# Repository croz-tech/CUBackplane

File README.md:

# Control Universal 4-Slot DIN41612 Backplane
***Note: Early preview only... at this time this board has not been fabricated/tested***

A 4 slot DIN 41612 backplane for use with the EuroBEEB and compatible cards

- Designed in KiCAD, in addition to giving 4x DIN connectors on a 1" (5HP spacing) allowing mounting in a 24HP enclosure with 2HP blanking plates at either end.
- Board has pads for power supply inputs (actually only +5V and GND are needed for a standard EuroBEEB) and test points for access to all Data, Control and Address lines.  These TPs are labelled on the under/back side for easy access when this is mounted in a rack.  The TPs are on a 0.1" pitch, so headers can be used if desired.
- Board is <100x100mm so should be low-cost fabrication.

Note that this isn't strictly a 'backplane' in the DIN enclosure sense.  Rather than mounting the PCB to 'backplane' fixtures in an enclosure, the PCB should simply be soldered across the row of vertical DIN female connectors and then the connectors mounted to specific connector mounting rails.  Please take this into consideration if ordering enclosure parts from Verotec or your preferred enclosure supplier.

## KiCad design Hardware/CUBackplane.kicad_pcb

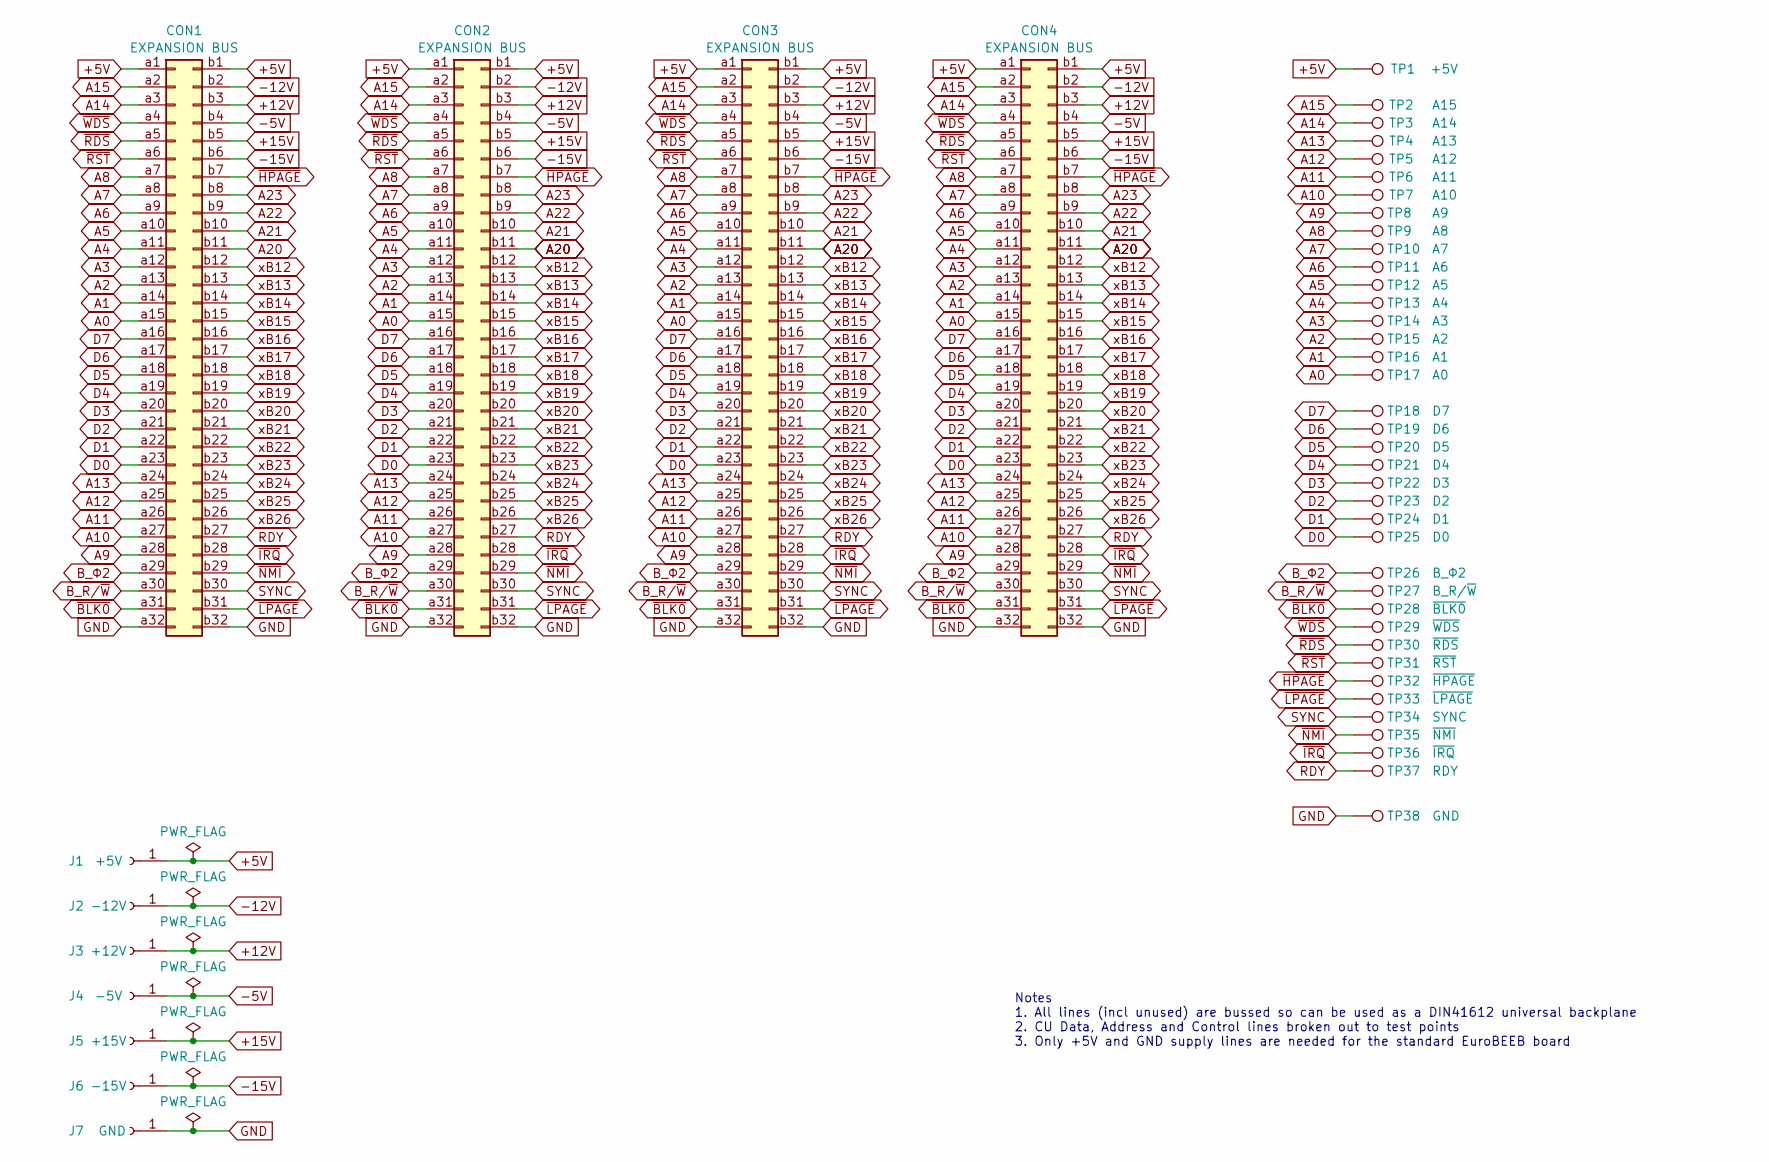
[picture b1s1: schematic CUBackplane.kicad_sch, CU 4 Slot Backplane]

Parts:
CON1, CON2, CON3, CON4: EXPANSION BUS; DIN41612_B_2x32_Female_Vertical_THT
J1: +5V; TestPoint_THTPad_D3.0mm_Drill1.5mm
J2: -12V; TestPoint_THTPad_D2.0mm_Drill1.0mm
J3: +12V; TestPoint_THTPad_D2.0mm_Drill1.0mm
J4: -5V; TestPoint_THTPad_D2.0mm_Drill1.0mm
J5: +15V; TestPoint_THTPad_D2.0mm_Drill1.0mm
J6: -15V; TestPoint_THTPad_D2.0mm_Drill1.0mm
J7: GND; TestPoint_THTPad_D3.0mm_Drill1.5mm
TP1: +5V; TestPoint_THTPad_D1.5mm_Drill0.7mm
TP2: A15; TestPoint_THTPad_D1.5mm_Drill0.7mm
TP3: A14; TestPoint_THTPad_D1.5mm_Drill0.7mm
TP4: A13; TestPoint_THTPad_D1.5mm_Drill0.7mm
TP5: A12; TestPoint_THTPad_D1.5mm_Drill0.7mm
TP6: A11; TestPoint_THTPad_D1.5mm_Drill0.7mm
TP7: A10; TestPoint_THTPad_D1.5mm_Drill0.7mm
TP8: A9; TestPoint_THTPad_D1.5mm_Drill0.7mm
TP9: A8; TestPoint_THTPad_D1.5mm_Drill0.7mm
TP10: A7; TestPoint_THTPad_D1.5mm_Drill0.7mm
TP11: A6; TestPoint_THTPad_D1.5mm_Drill0.7mm
TP12: A5; TestPoint_THTPad_D1.5mm_Drill0.7mm
TP13: A4; TestPoint_THTPad_D1.5mm_Drill0.7mm
TP14: A3; TestPoint_THTPad_D1.5mm_Drill0.7mm
TP15: A2; TestPoint_THTPad_D1.5mm_Drill0.7mm
TP16: A1; TestPoint_THTPad_D1.5mm_Drill0.7mm
TP17: A0; TestPoint_THTPad_D1.5mm_Drill0.7mm
TP18: D7; TestPoint_THTPad_D1.5mm_Drill0.7mm
TP19: D6; TestPoint_THTPad_D1.5mm_Drill0.7mm
TP20: D5; TestPoint_THTPad_D1.5mm_Drill0.7mm
TP21: D4; TestPoint_THTPad_D1.5mm_Drill0.7mm
TP22: D3; TestPoint_THTPad_D1.5mm_Drill0.7mm
TP23: D2; TestPoint_THTPad_D1.5mm_Drill0.7mm
TP24: D1; TestPoint_THTPad_D1.5mm_Drill0.7mm
TP25: D0; TestPoint_THTPad_D1.5mm_Drill0.7mm
TP26: B_Φ2; TestPoint_THTPad_D1.5mm_Drill0.7mm
TP27: B_R/~{W}; TestPoint_THTPad_D1.5mm_Drill0.7mm
TP28: ~{BLK0}; TestPoint_THTPad_D1.5mm_Drill0.7mm
TP29: ~{WDS}; TestPoint_THTPad_D1.5mm_Drill0.7mm
TP30: ~{RDS}; TestPoint_THTPad_D1.5mm_Drill0.7mm
TP31: ~{RST}; TestPoint_THTPad_D1.5mm_Drill0.7mm
TP32: ~{HPAGE}; TestPoint_THTPad_D1.5mm_Drill0.7mm
TP33: ~{LPAGE}; TestPoint_THTPad_D1.5mm_Drill0.7mm
TP34: SYNC; TestPoint_THTPad_D1.5mm_Drill0.7mm
TP35: ~{NMI}; TestPoint_THTPad_D1.5mm_Drill0.7mm
TP36: ~{IRQ}; TestPoint_THTPad_D1.5mm_Drill0.7mm
TP37: RDY; TestPoint_THTPad_D1.5mm_Drill0.7mm
TP38: GND; TestPoint_THTPad_D1.5mm_Drill0.7mm

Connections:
+5V: CON1.a1, CON1.b1, CON2.a1, CON2.b1, CON3.a1, CON3.b1, CON4.a1, CON4.b1, J1.1, TP1.1
+12V: CON1.b3, CON2.b3, CON3.b3, CON4.b3, J3.1
+15V: CON1.b5, CON2.b5, CON3.b5, CON4.b5, J5.1
-5V: CON1.b4, CON2.b4, CON3.b4, CON4.b4, J4.1
-12V: CON1.b2, CON2.b2, CON3.b2, CON4.b2, J2.1
-15V: CON1.b6, CON2.b6, CON3.b6, CON4.b6, J6.1
A0: CON1.a15, CON2.a15, CON3.a15, CON4.a15, TP17.1
A1: CON1.a14, CON2.a14, CON3.a14, CON4.a14, TP16.1
A2: CON1.a13, CON2.a13, CON3.a13, CON4.a13, TP15.1
A3: CON1.a12, CON2.a12, CON3.a12, CON4.a12, TP14.1
A4: CON1.a11, CON2.a11, CON3.a11, CON4.a11, TP13.1
A5: CON1.a10, CON2.a10, CON3.a10, CON4.a10, TP12.1
A6: CON1.a9, CON2.a9, CON3.a9, CON4.a9, TP11.1
A7: CON1.a8, CON2.a8, CON3.a8, CON4.a8, TP10.1
A8: CON1.a7, CON2.a7, CON3.a7, CON4.a7, TP9.1
A9: CON1.a28, CON2.a28, CON3.a28, CON4.a28, TP8.1
A10: CON1.a27, CON2.a27, CON3.a27, CON4.a27, TP7.1
A11: CON1.a26, CON2.a26, CON3.a26, CON4.a26, TP6.1
A12: CON1.a25, CON2.a25, CON3.a25, CON4.a25, TP5.1
A13: CON1.a24, CON2.a24, CON3.a24, CON4.a24, TP4.1
A14: CON1.a3, CON2.a3, CON3.a3, CON4.a3, TP3.1
A15: CON1.a2, CON2.a2, CON3.a2, CON4.a2, TP2.1
A20: CON1.b11, CON2.b11, CON3.b11, CON4.b11
A21: CON1.b10, CON2.b10, CON3.b10, CON4.b10
A22: CON1.b9, CON2.b9, CON3.b9, CON4.b9
A23: CON1.b8, CON2.b8, CON3.b8, CON4.b8
B_R/~W: CON1.a30, CON2.a30, CON3.a30, CON4.a30, TP27.1
B_Φ2: CON1.a29, CON2.a29, CON3.a29, CON4.a29, TP26.1
D0: CON1.a23, CON2.a23, CON3.a23, CON4.a23, TP25.1
D1: CON1.a22, CON2.a22, CON3.a22, CON4.a22, TP24.1
D2: CON1.a21, CON2.a21, CON3.a21, CON4.a21, TP23.1
D3: CON1.a20, CON2.a20, CON3.a20, CON4.a20, TP22.1
D4: CON1.a19, CON2.a19, CON3.a19, CON4.a19, TP21.1
D5: CON1.a18, CON2.a18, CON3.a18, CON4.a18, TP20.1
D6: CON1.a17, CON2.a17, CON3.a17, CON4.a17, TP19.1
D7: CON1.a16, CON2.a16, CON3.a16, CON4.a16, TP18.1
GND: CON1.a32, CON1.b32, CON2.a32, CON2.b32, CON3.a32, CON3.b32, CON4.a32, CON4.b32, J7.1, TP38.1
RDY: CON1.b27, CON2.b27, CON3.b27, CON4.b27, TP37.1
SYNC: CON1.b30, CON2.b30, CON3.b30, CON4.b30, TP34.1
xB12: CON1.b12, CON2.b12, CON3.b12, CON4.b12
xB13: CON1.b13, CON2.b13, CON3.b13, CON4.b13
xB14: CON1.b14, CON2.b14, CON3.b14, CON4.b14
xB15: CON1.b15, CON2.b15, CON3.b15, CON4.b15
xB16: CON1.b16, CON2.b16, CON3.b16, CON4.b16
xB17: CON1.b17, CON2.b17, CON3.b17, CON4.b17
xB18: CON1.b18, CON2.b18, CON3.b18, CON4.b18
xB19: CON1.b19, CON2.b19, CON3.b19, CON4.b19
xB20: CON1.b20, CON2.b20, CON3.b20, CON4.b20
xB21: CON1.b21, CON2.b21, CON3.b21, CON4.b21
xB22: CON1.b22, CON2.b22, CON3.b22, CON4.b22
xB23: CON1.b23, CON2.b23, CON3.b23, CON4.b23
xB24: CON1.b24, CON2.b24, CON3.b24, CON4.b24
xB25: CON1.b25, CON2.b25, CON3.b25, CON4.b25
xB26: CON1.b26, CON2.b26, CON3.b26, CON4.b26
~BLK0: CON1.a31, CON2.a31, CON3.a31, CON4.a31, TP28.1
~HPAGE: CON1.b7, CON2.b7, CON3.b7, CON4.b7, TP32.1
~IRQ: CON1.b28, CON2.b28, CON3.b28, CON4.b28, TP36.1
~LPAGE: CON1.b31, CON2.b31, CON3.b31, CON4.b31, TP33.1
~NMI: CON1.b29, CON2.b29, CON3.b29, CON4.b29, TP35.1
~RDS: CON1.a5, CON2.a5, CON3.a5, CON4.a5, TP30.1
~RST: CON1.a6, CON2.a6, CON3.a6, CON4.a6, TP31.1
~WDS: CON1.a4, CON2.a4, CON3.a4, CON4.a4, TP29.1

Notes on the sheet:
Notes 1. All lines (incl unused) are bussed so can be used as a DIN41612 universal backplane 2. CU Data, Address and Control lines broken out to test points 3. Only +5V and GND supply lines are needed for the standard EuroBEEB board

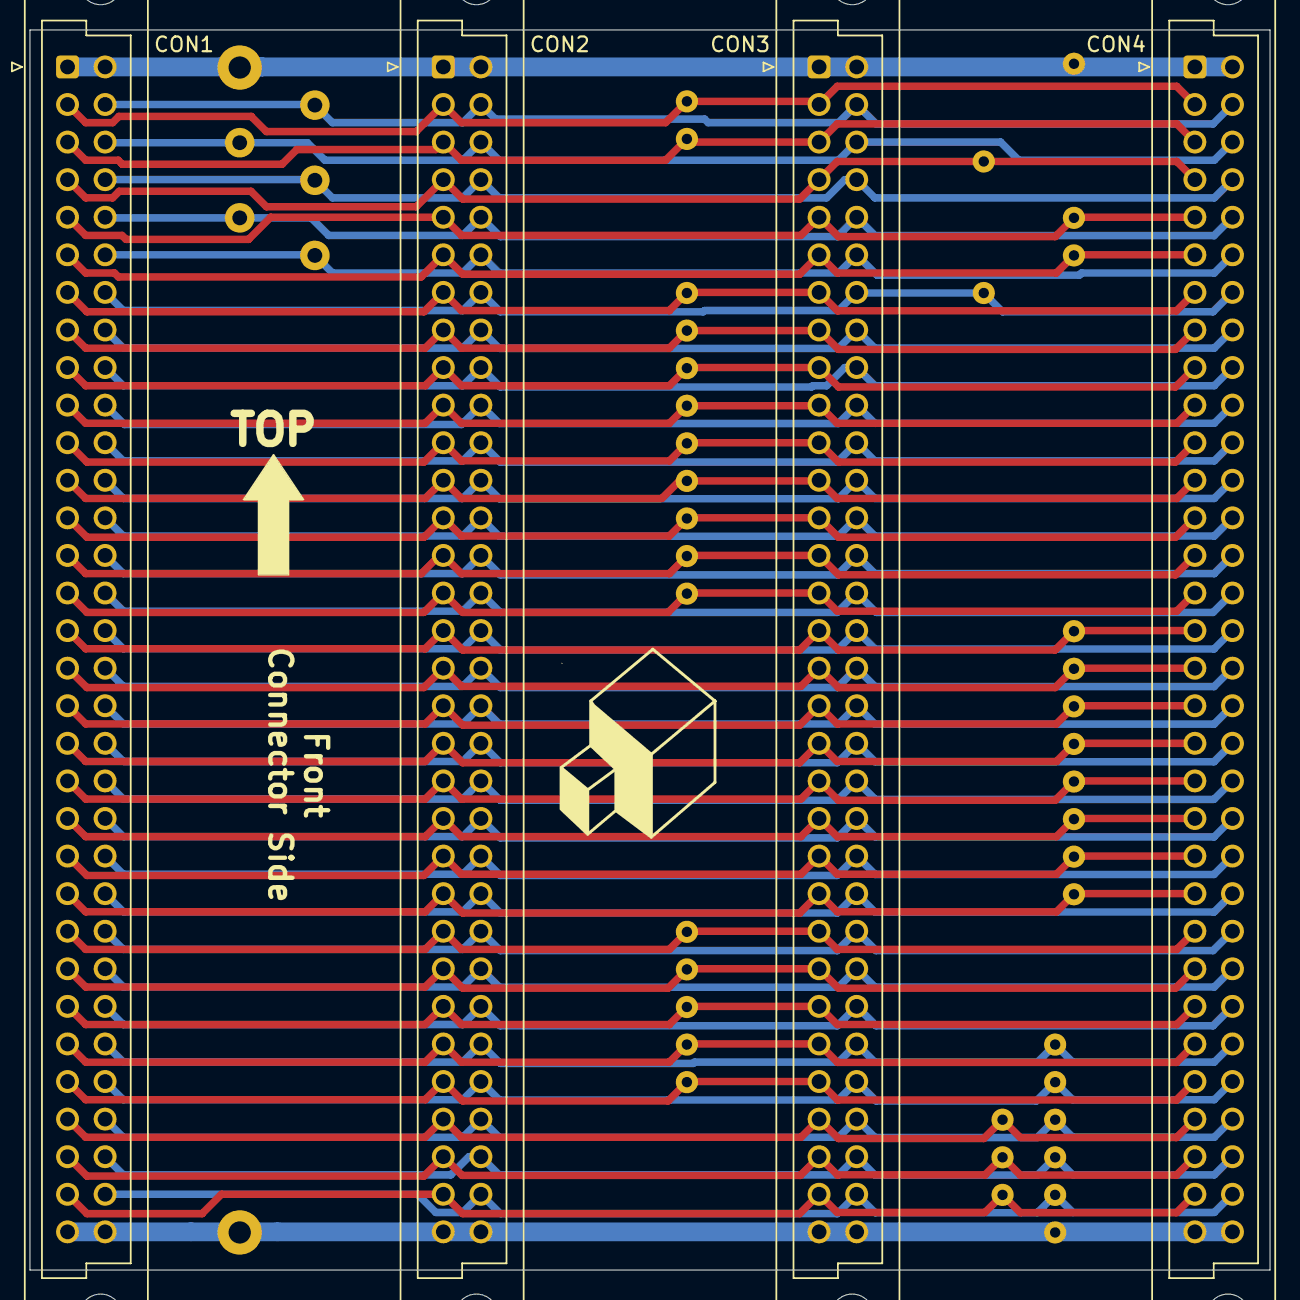
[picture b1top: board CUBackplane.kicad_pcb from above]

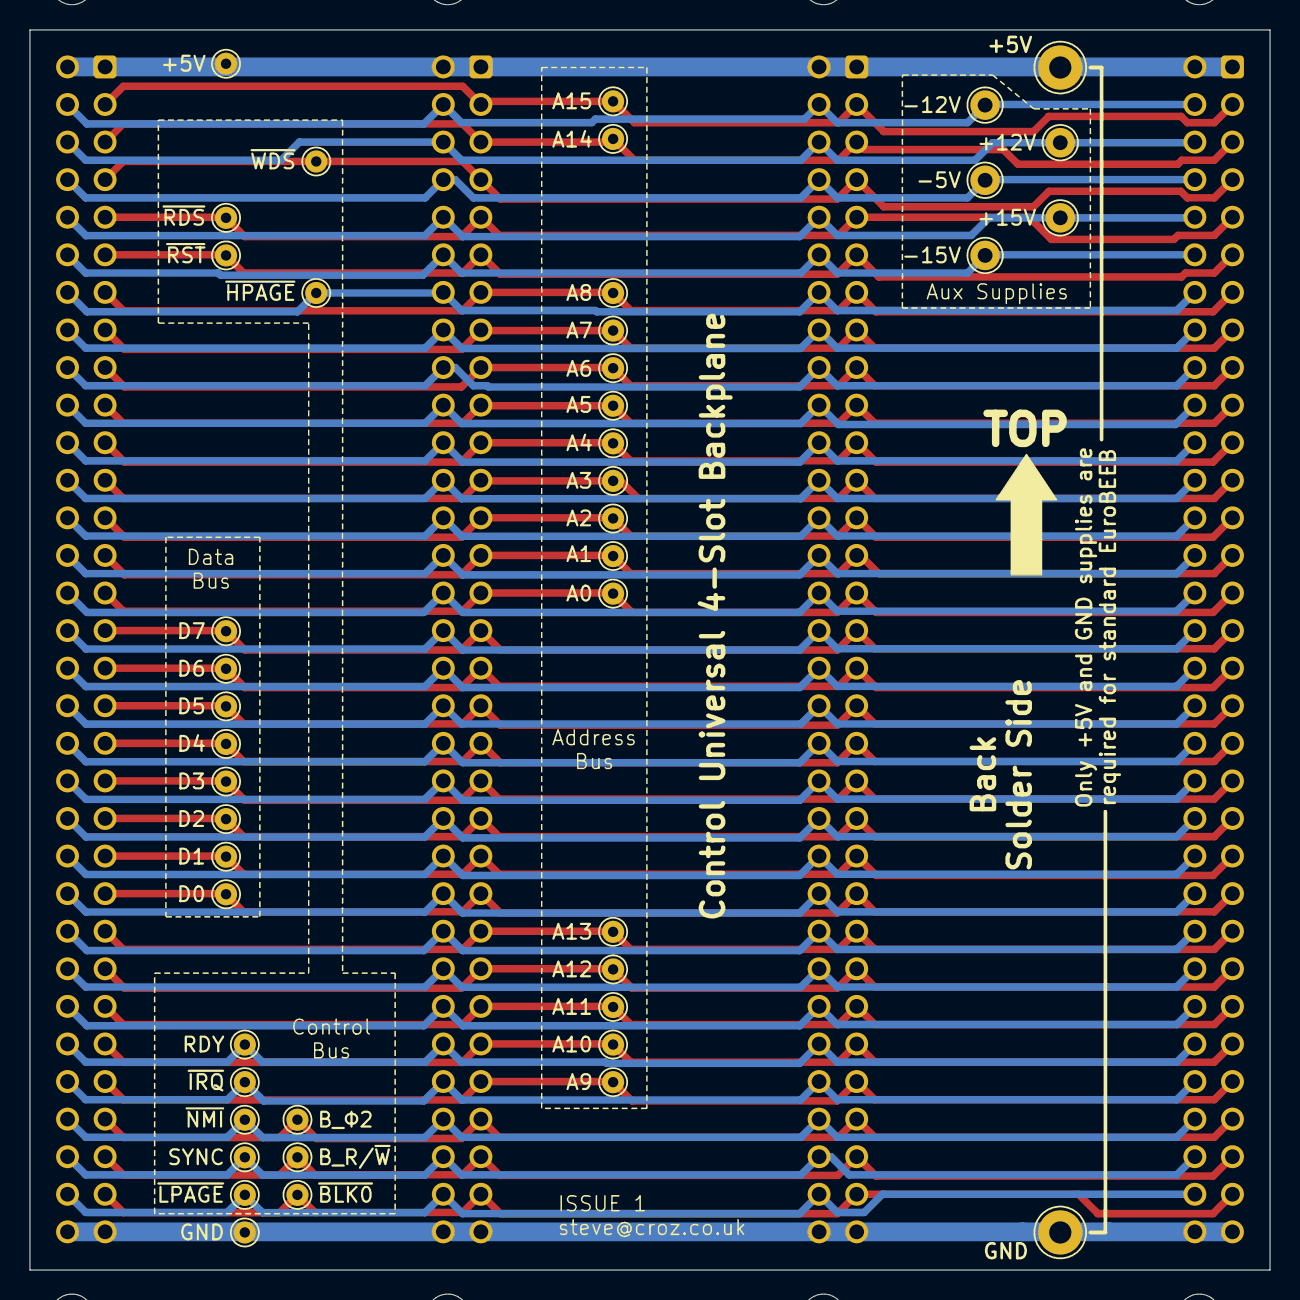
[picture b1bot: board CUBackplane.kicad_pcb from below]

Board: 2 copper layers, 83.8 x 83.8 mm, 49 parts (45 on the bottom side), 62 nets.

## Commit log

2025-03-27 Initial version
2025-03-27 Added images
2025-03-27 Smaller images
2025-03-27 Aligned, updated alt text
2025-03-27 Added warning
2025-03-27 Corrected board outline to 3.3x3.3
2025-03-27 Moved connector references
